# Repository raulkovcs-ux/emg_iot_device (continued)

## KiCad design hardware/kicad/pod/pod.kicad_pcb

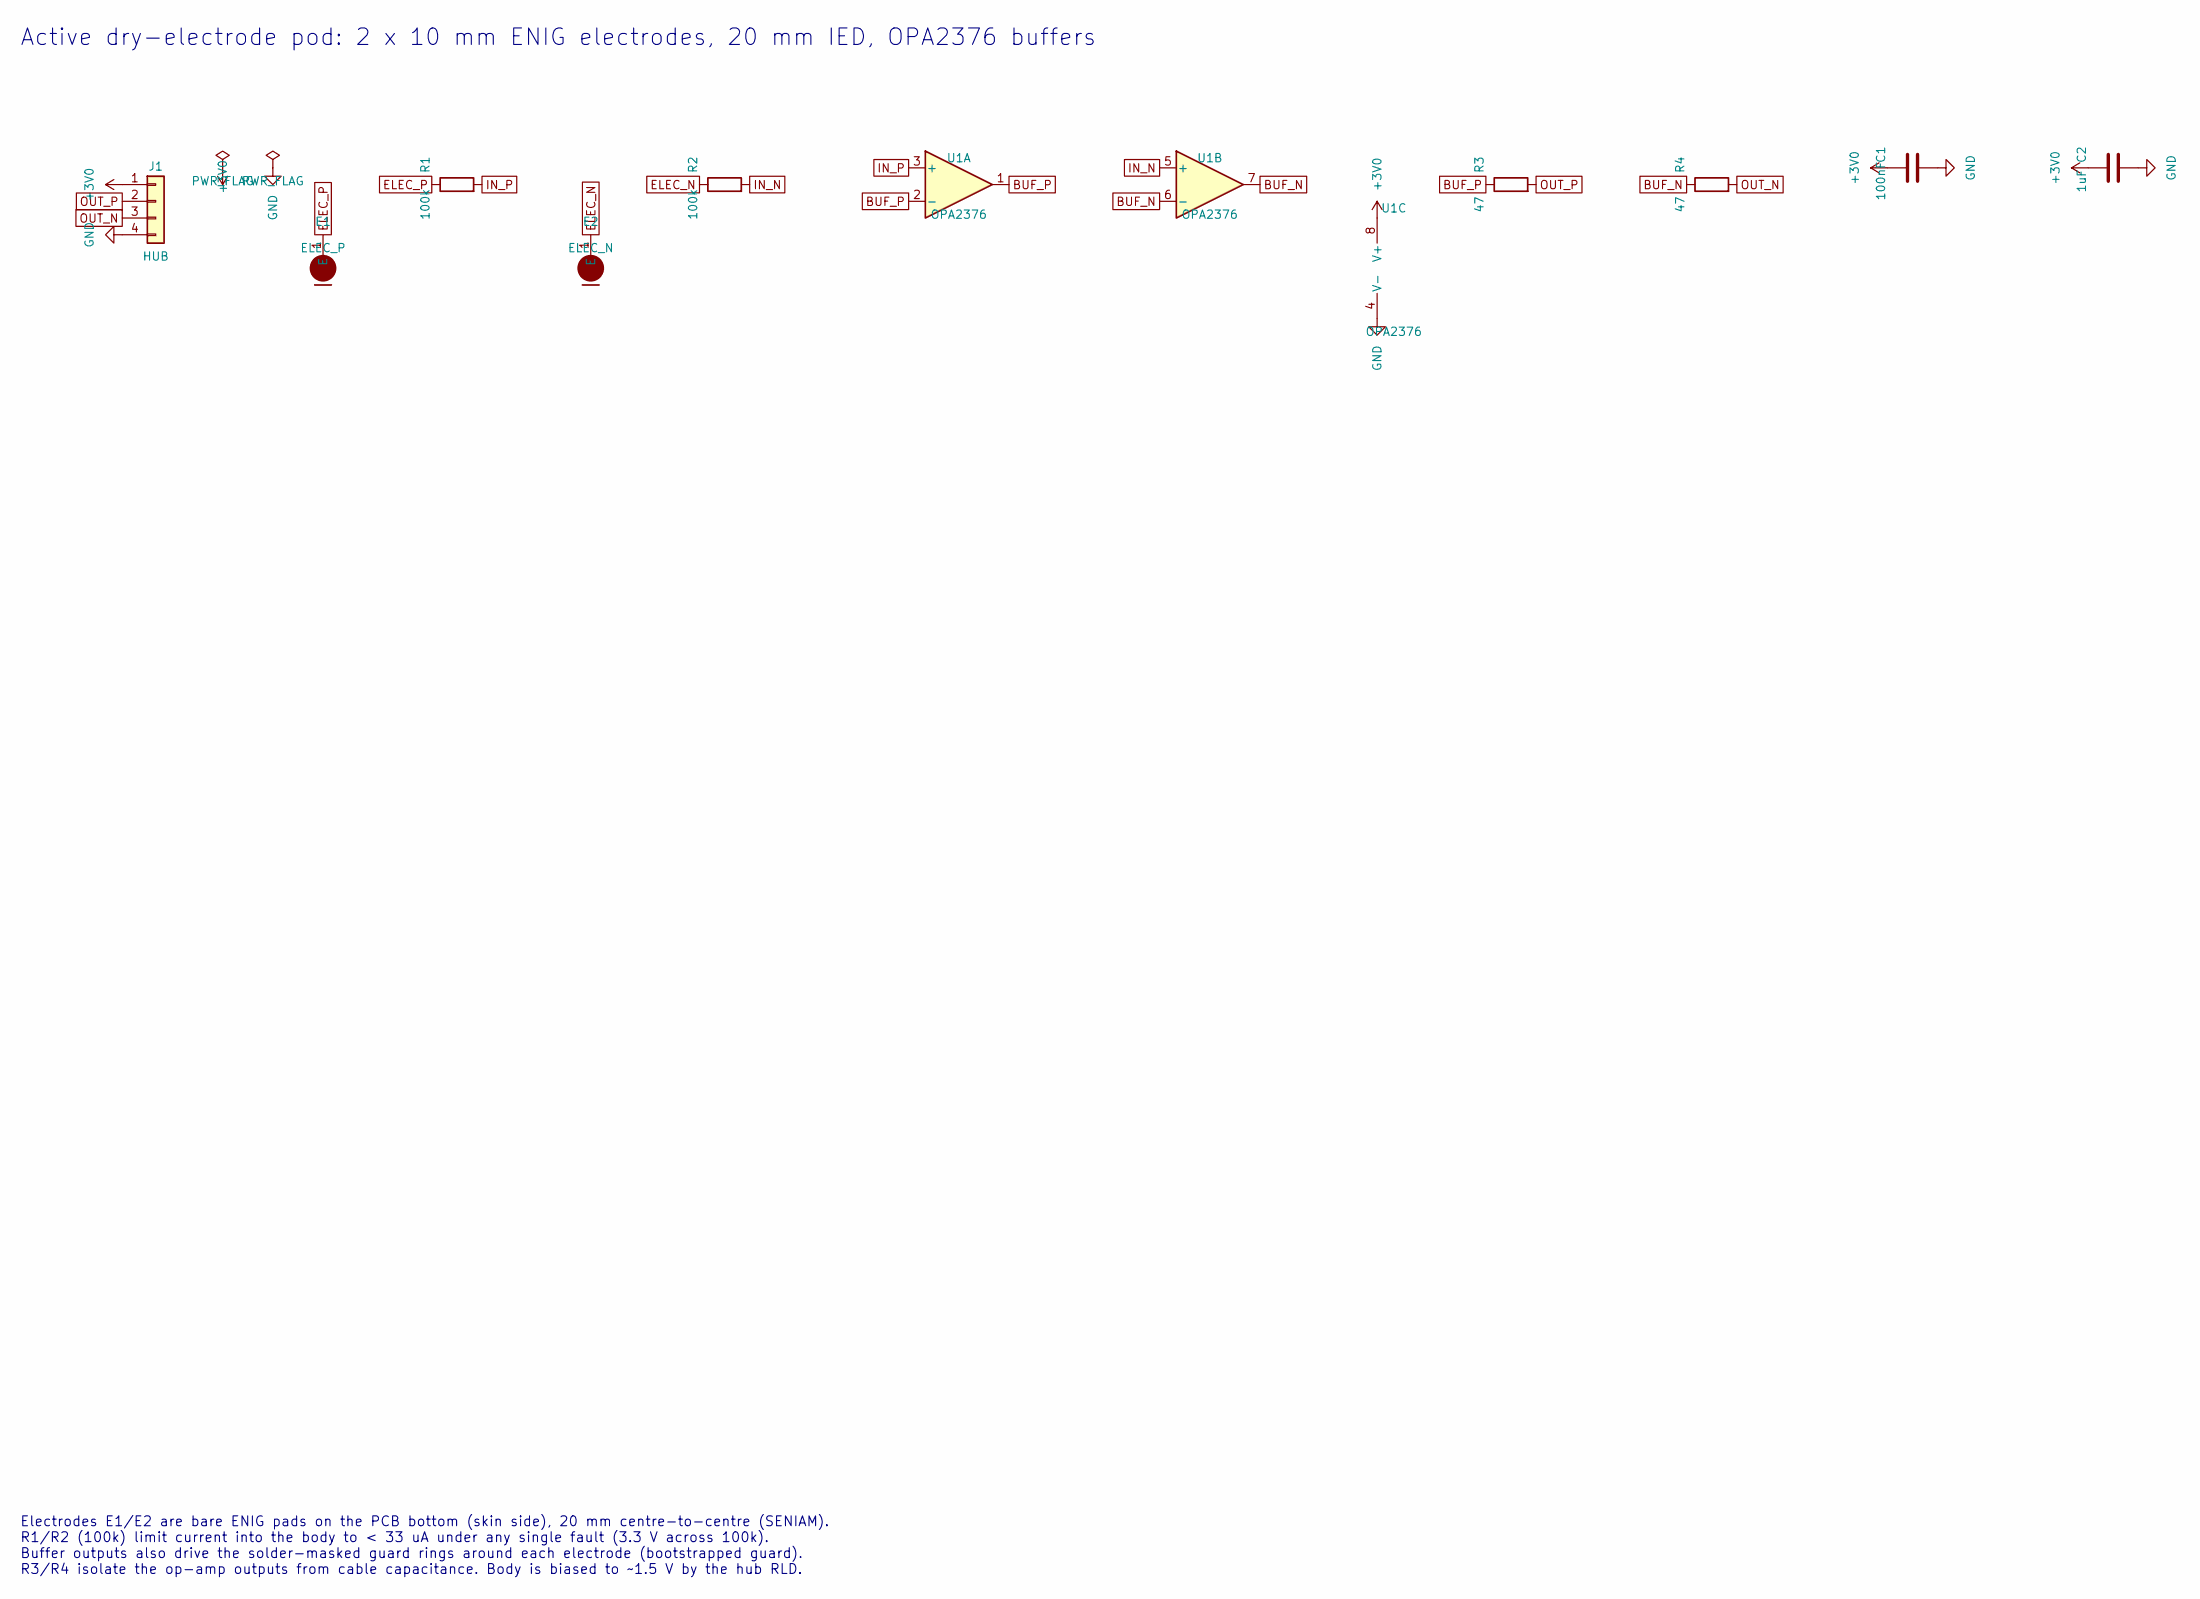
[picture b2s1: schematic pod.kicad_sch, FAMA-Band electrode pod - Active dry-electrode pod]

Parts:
C1: 100nF; C_0603_1608Metric
C2: 1uF; C_0603_1608Metric
E1: ELEC_P; DryElectrode_D10mm
E2: ELEC_N; DryElectrode_D10mm
J1: HUB; JST_GH_SM04B-GHS-TB_1x04-1MP_P1.25mm_Horizontal; MPN SM04B-GHS-TB(LF)(SN)
R1, R2: 100k; R_0603_1608Metric
R3, R4: 47; R_0603_1608Metric
U1: OPA2376; VSSOP-8_3.0x3.0mm_P0.65mm; MPN OPA2376AIDGKR

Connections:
+3V0: C1.1, C2.1, J1.1, U1.8 (V+)
BUF_N: R4.1, U1.6 (-), U1.7
BUF_P: R3.1, U1.1, U1.2 (-)
ELEC_N: E2.1, R2.1
ELEC_P: E1.1, R1.1
GND: C1.2, C2.2, J1.4, U1.4 (V-)
IN_N: R2.2, U1.5 (+)
IN_P: R1.2, U1.3 (+)
OUT_N: J1.3, R4.2
OUT_P: J1.2, R3.2

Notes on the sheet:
Active dry-electrode pod: 2 x 10 mm ENIG electrodes, 20 mm IED, OPA2376 buffers
Electrodes E1/E2 are bare ENIG pads on the PCB bottom (skin side), 20 mm centre-to-centre (SENIAM). R1/R2 (100k) limit current into the body to < 33 uA under any single fault (3.3 V across 100k). Buffer outputs also drive the solder-masked guard rings around each electrode (bootstrapped guard). R3/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

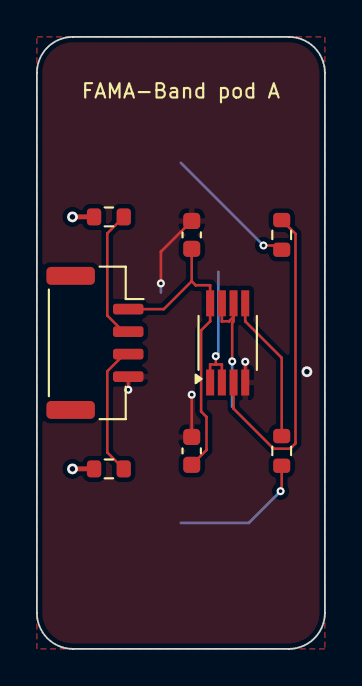
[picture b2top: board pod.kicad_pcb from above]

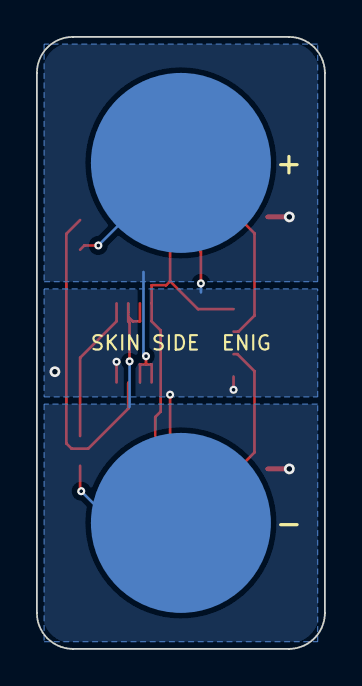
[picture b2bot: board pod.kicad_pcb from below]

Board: 2 copper layers, 16.0 x 34.0 mm, 10 parts (2 on the bottom side), 10 nets.

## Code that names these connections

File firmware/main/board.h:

/* FAMA-Band hub rev A pin map. Must match hardware/gen/hub.py (MCU sheet). */
#pragma once
#include "driver/gpio.h"

/* ADS1298 on SPI2 */
#define PIN_AFE_SCLK   GPIO_NUM_12
#define PIN_AFE_DIN    GPIO_NUM_11   /* MCU MOSI -> ADS DIN */
#define PIN_AFE_DOUT   GPIO_NUM_13   /* ADS DOUT -> MCU MISO */
#define PIN_AFE_CS     GPIO_NUM_10
#define PIN_AFE_DRDY   GPIO_NUM_9
#define PIN_AFE_START  GPIO_NUM_14
#define PIN_AFE_RESET  GPIO_NUM_21
#define PIN_AFE_PWDN   GPIO_NUM_47
#define PIN_AFE_EN     GPIO_NUM_48   /* LP5907 enable via R; hardware-gated off by VBUS */

/* I2C: LSM6DSL (0x6A) + LC709203F (0x0B) */
#define PIN_I2C_SDA    GPIO_NUM_4
#define PIN_I2C_SCL    GPIO_NUM_5
#define PIN_IMU_INT1   GPIO_NUM_6
#define PIN_FG_ALRT    GPIO_NUM_7

#define PIN_VBUS_DET   GPIO_NUM_15   /* high = USB power present (2/3 VBUS divider) */
#define PIN_LED_G      GPIO_NUM_17
#define PIN_LED_B      GPIO_NUM_18
#define PIN_BTN        GPIO_NUM_0    /* BOOT/USER, active low */

/* microSD, 4-bit SDMMC through the GPIO matrix */
#define PIN_SD_CLK     GPIO_NUM_39
#define PIN_SD_CMD     GPIO_NUM_38
#define PIN_SD_D0      GPIO_NUM_40
#define PIN_SD_D1      GPIO_NUM_41
#define PIN_SD_D2      GPIO_NUM_42
#define PIN_SD_D3      GPIO_NUM_2
#define PIN_SD_DET     GPIO_NUM_1    /* low = card inserted (DM3AT detect switch to GND) */

#define AFE_SPI_HZ     (8 * 1000 * 1000)

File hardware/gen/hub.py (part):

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    c.newrow()
    c.nc(u, "27", "29")
    c.connect("GND", u["RESV1"], u["DAISY_IN"], u["CLKSEL"])
    for sig, pin in (("AFE_DIN", "DIN"), ("AFE_PWDN", "~{PWDN}"), ("AFE_RESET", "~{RESET}"), ("AFE_CLK", "CLK"),
                     ("AFE_START", "START"), ("AFE_CS", "~{CS}"), ("AFE_SCLK", "SCLK"), ("AFE_DOUT", "DOUT"),
                     ("AFE_DRDY", "~{DRDY}")):
        c.connect(sig, u[pin])
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    c.connect("GND", m["1"], m["40"], m["41"]); c.connect("+3V3", m["2"])
    c.connect("ESP_EN", m["EN"])
    c.R("10k", "+3V3", "ESP_EN"); c.C("1uF", "ESP_EN", "GND")
    gpio = {"IO12": "AFE_SCLK", "IO11": "AFE_DIN", "IO13": "AFE_DOUT", "IO10": "AFE_CS", "IO9": "AFE_DRDY",
            "IO14": "AFE_START", "IO21": "AFE_RESET", "IO47": "AFE_PWDN", "IO48": "AFE_EN_MCU",
            "IO4": "I2C_SDA", "IO5": "I2C_SCL", "IO6": "IMU_INT1", "IO7": "FG_ALRT", "IO15": "VBUS_DET",
            "IO17": "LED_G", "IO18": "LED_B", "IO19": "USB_D-", "IO20": "USB_D+",
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    c.newrow()
    c.C("10uF", "+3V3", "GND", "0603"); c.C("100nF", "+3V3", "GND")

    for net, label in (("ESP_EN", "RESET"), ("BOOT", "BOOT/USER")):
        b = c.part("SW", "Switch:SW_Push", label, "Button_Switch_SMD:SW_Push_1P1T_NO_CK_KMR2",
                   mpn="KMR221GLFS", manufacturer="C&K", desc="Tactile switch")
        c.connect(net, b["1"]); c.connect("GND", b["2"])
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    c.newrow()
    sd = c.part("J", "Connector:Micro_SD_Card_Det_Hirose_DM3AT", "microSD", "Connector_Card:microSD_HC_Hirose_DM3AT-SF-PEJM5",
                mpn="DM3AT-SF-PEJM5", manufacturer="Hirose", desc="microSD socket with card detect")
    for net, pin in (("SD_D2", "1"), ("SD_D3", "2"), ("SD_CMD", "3"), ("+3V3", "4"), ("SD_CLK", "5"), ("GND", "6"),
                     ("SD_D0", "7"), ("SD_D1", "8"), ("SD_DET", "9"), ("GND", "10"), ("GND", "11")):
        c.connect(net, sd[pin])
    for net in ("SD_CMD", "SD_D0", "SD_D1", "SD_D2", "SD_D3", "SD_DET"):
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           "prosthetist enables them (firmware TD mode). Hand powered from its own battery.")
    j = c.part("J", "Connector_Generic:Conn_01x06", "HAND", "Connector_JST:JST_GH_SM06B-GHS-TB_1x06-1MP_P1.25mm_Horizontal",
               mpn="SM06B-GHS-TB(LF)(SN)", manufacturer="JST", desc="Terminal-device interface")
    c.connect("TD_TX_PIN", m["TXD0"]); c.connect("TD_RX_PIN", m["RXD0"])
    c.R("330", "TD_TX_PIN", "TD_TX"); c.R("330", "TD_RX", "TD_RX_PIN")
    c.connect("TD_PWM1", m["IO16"]); c.connect("TD_PWM2", m["IO8"])
    for k in (1, 2):
        c.R("10k", f"TD_PWM{k}", f"TD_AN{k}")
        c.C("1uF", f"TD_AN{k}", "GND", "0603")
    for net, pin in (("+3V3", "1"), ("TD_TX", "2"), ("TD_RX", "3"), ("TD_AN1", "4"), ("TD_AN2", "5"), ("GND", "6")):
        c.connect(net, j[pin])
    c.R("100k", "TD_RX", "+3V3")  # idle-high when nothing is connected

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
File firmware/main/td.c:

/* Terminal-device output: FAMA-Net decisions -> prosthetic hand controller. */
#include "sdkconfig.h"
#if CONFIG_FAMA_BOARD_SOCKET
#include "td.h"

#include <stdatomic.h>

#include "driver/ledc.h"
#include "driver/uart.h"
#include "esp_log.h"
#include "esp_timer.h"
#include "fama_dsp.h"
#include "freertos/FreeRTOS.h"
#include "freertos/task.h"
#include "sdkconfig.h"

static const char *TAG = "td";
#define PIN_TD_TX 43
#define PIN_TD_RX 44
#define PIN_TD_PWM1 16
#define PIN_TD_PWM2 8
#define PWM_BITS LEDC_TIMER_10_BIT
#define PWM_MAX ((1 << 10) - 1)
#define STALE_US (300 * 1000)   /* no result for 300 ms -> outputs to 0 */

static fama_td_t s_td;
static atomic_bool s_on;
static atomic_llong s_last_us;
static uint32_t s_seq;
static portMUX_TYPE s_mux = portMUX_INITIALIZER_UNLOCKED;

static void set_out(const float out[2])
{
    for (int k = 0; k < 2; k++) {
        uint32_t d = (uint32_t)(out[k] * PWM_MAX + 0.5f);
        ledc_set_duty(LEDC_LOW_SPEED_MODE, (ledc_channel_t)k, d > PWM_MAX ? PWM_MAX : d);
        ledc_update_duty(LEDC_LOW_SPEED_MODE, (ledc_channel_t)k);
    }
}

static void watchdog_task(void *arg)
{
    float zero[2];
    for (;;) {
        vTaskDelay(pdMS_TO_TICKS(20));
        if (esp_timer_get_time() - atomic_load(&s_last_us) > STALE_US || !atomic_load(&s_on)) {
            taskENTER_CRITICAL(&s_mux);
            fama_td_stale(&s_td, zero);
            taskEXIT_CRITICAL(&s_mux);
            set_out(zero);
        }
    }
}

void td_init(void)
{
    ledc_timer_config_t t = { .speed_mode = LEDC_LOW_SPEED_MODE, .duty_resolution = PWM_BITS, .timer_num = LEDC_TIMER_0,
                              .freq_hz = 20000, .clk_cfg = LEDC_AUTO_CLK };
    ESP_ERROR_CHECK(ledc_timer_config(&t));
    const int pins[2] = { PIN_TD_PWM1, PIN_TD_PWM2 };
    for (int k = 0; k < 2; k++) {
        ledc_channel_config_t ch = { .gpio_num = pins[k], .speed_mode = LEDC_LOW_SPEED_MODE, .channel = (ledc_channel_t)k,
                                     .timer_sel = LEDC_TIMER_0, .duty = 0, .hpoint = 0 };
        ESP_ERROR_CHECK(ledc_channel_config(&ch));
    }
    uart_config_t uc = { .baud_rate = 115200, .data_bits = UART_DATA_8_BITS, .parity = UART_PARITY_DISABLE,
                         .stop_bits = UART_STOP_BITS_1, .flow_ctrl = UART_HW_FLOWCTRL_DISABLE, .source_clk = UART_SCLK_DEFAULT };
    ESP_ERROR_CHECK(uart_driver_install(UART_NUM_0, 256, 1024, 0, NULL, 0));
    ESP_ERROR_CHECK(uart_param_config(UART_NUM_0, &uc));
    ESP_ERROR_CHECK(uart_set_pin(UART_NUM_0, PIN_TD_TX, PIN_TD_RX, UART_PIN_NO_CHANGE, UART_PIN_NO_CHANGE));
    fama_td_init(&s_td, CONFIG_FAMA_TD_OPEN_CLASS, CONFIG_FAMA_TD_CLOSE_CLASS);
#ifdef CONFIG_FAMA_TD_ENABLE_AT_BOOT
    atomic_store(&s_on, true);
#else
    atomic_store(&s_on, false);
#endif
    xTaskCreatePinnedToCore(watchdog_task, "td_wd", 2048, NULL, 9, NULL, 0);
    ESP_LOGI(TAG, "hand interface ready, outputs %s (open=class %d, close=class %d)",
             atomic_load(&s_on) ? "ENABLED" : "disabled", CONFIG_FAMA_TD_OPEN_CLASS, CONFIG_FAMA_TD_CLOSE_CLASS);
}

void td_enable(bool on)
{
    atomic_store(&s_on, on);
    ESP_LOGW(TAG, "hand outputs %s", on ? "ENABLED" : "disabled");
}

bool td_enabled(void) { return atomic_load(&s_on); }

void td_on_result(const fb_result_t *res, const float *probs, int n_classes)
{
    uint8_t pkt[FB_HDR + sizeof(fb_result_t) + FB_CRC];
    size_t n = fb_pack(pkt, sizeof(pkt), FB_T_RESULT, s_seq++, res->window, 1, res, sizeof(*res));
    uart_write_bytes(UART_NUM_0, pkt, n);   /* decisions always visible to the hand controller */
    if (!atomic_load(&s_on)) return;
    float out[2];
    taskENTER_CRITICAL(&s_mux);
    fama_td_update(&s_td, probs, n_classes, out);
    taskEXIT_CRITICAL(&s_mux);
    set_out(out);
    atomic_store(&s_last_us, esp_timer_get_time());
}
#endif /* CONFIG_FAMA_BOARD_SOCKET */
